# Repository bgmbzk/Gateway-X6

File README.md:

# Gateway-X6 — 6 Katmanlı STM32 Yüksek Hızlı Donanım Tasarımı

Gateway-X6; STM32 mikrokontrolcü mimarisi, harici SDRAM arayüzü ve endüstriyel haberleşme hatlarını bir araya getiren, sinyal bütünlüğü (Signal Integrity) ve güç dağıtımı (Power Distribution) önceliklendirilerek tasarlanmış 6 katmanlı (6-layer) bir PCB projesidir.

---

## 📸 Proje Görselleri

### 1. 3D Kart Görünümü

### 2. PCB Katman Çizimi ve Yönlendirme

### 3. Şematik Tasarım

---

## Proje Motivasyonu ve Öğrenim Hedefleri

Bu proje; hem profesyonel donanım tasarımı standartlarını pratiğe dökmek hem de karmaşık mimarilerle çalışırken karşılaşılan zorlukları bizzat tecrübe etmek amacıyla geliştirilmiştir:

- **STM32 Tasarım Standartları:** STM32 mikrokontrolcü ekosisteminin yüksek hızlı çevre birimleri, kristal osilatör hatları ve decoupling (dekaplaj) kondansatör yerleşim standartlarını derinlemesine uygulamak.
- **6 Katmanlı Yığın Yapısı (Stackup):** 2 veya 4 katmanlı yapıların ötesine geçerek, gürültü bağışıklığı ve kesintisiz referans düzlemleri (GND/PWR plane) sunan 6 katmanlı mimariyi deneyimlemek.
- **Sinyal ve Adres Hatlarında Karmaşıklık Yönetimi:** STM32 ile SDRAM arasındaki FMC (Flexible Memory Controller) arayüzünde yer alan onlarca yüksek hızlı veri, adres ve kontrol hattını (FMC_SDCKE, FMC_SDCLK vb.) çakışmasız, izole ve doğru pin eşlemeleriyle yönlendirmek; bu süreçteki etiketleme (net management) ve adresleme karmaşıklıklarını büyük bir sabır ve hassasiyetle çözmek.

---

## Katman Mimarisi (6-Layer Stackup)

Kartın sinyal bütünlüğünü korumak ve EMC/EMI performansını artırmak için aşağıdaki katman dizilimi uygulanmıştır:

1. **Top Layer (`F.Cu`):** Yüksek Hızlı Sinyaller ve Komponent Yerleşimi
2. **GND Plane (`GND`):** Üst Katman İçin Kesintisiz Toprak Referans Düzlemi
3. **Inner Signal (`SIG1`):** İç Sinyal Yönlendirme Katmanı
4. **GND2 Plane (`GND2`):** Güç Katmanı İçin İkincil Toprak Düzlemi
5. **Power Plane (`PWR`):** $+3.3\text{V}$ Besleme Düzlemi
6. **Bottom Layer (`B.Cu`):** Alt Sinyaller ve Kalın Güç Yolları ($+24\text{V}$, $+5\text{V}$)

---

## Güç Mimarisi ve Yönlendirme

- **$+24\text{V}$ Filtreli Endüstriyel Giriş:** Giriş gürültülerini bastıran filtreleme yapısı ve $1.0\text{ mm}$ kalınlığında yüksek akım hatları.
- **Kademeli Regülasyon:** $+24\text{V} \rightarrow +5\text{V}$ ve $+5\text{V} \rightarrow +3.3\text{V}$ ana hatlar üzerinden kararlı voltaj dağıtımı.
- **Hassas Sinyal İzolasyonu:** Hızlı saat hatları (FMC_SDCLK) ve kontrol hatları, hata ayıklama (SWCLK) ve güç hatlarından izole edilerek cross-talk (çapraz gürültü) engellenmiştir.

---

## Proje Dizin Yapısı

```text
Gateway-X6/
├── Hardware/               # KiCad şematik ve PCB çizim dosyaları (.kicad_sch, .kicad_pcb)
├── Production/             # Üretime hazır Gerber ve Drill ZIP dosyaları
├── Docs/                   # Şematik PDF çıktıları ve teknik dokümanlar
├── Images/                 # Proje görselleri (Gateway-X6.3d.png, Gateway-X6.pcb.png, Gateway-X6.kch.png)
├── .gitignore
└── README.md

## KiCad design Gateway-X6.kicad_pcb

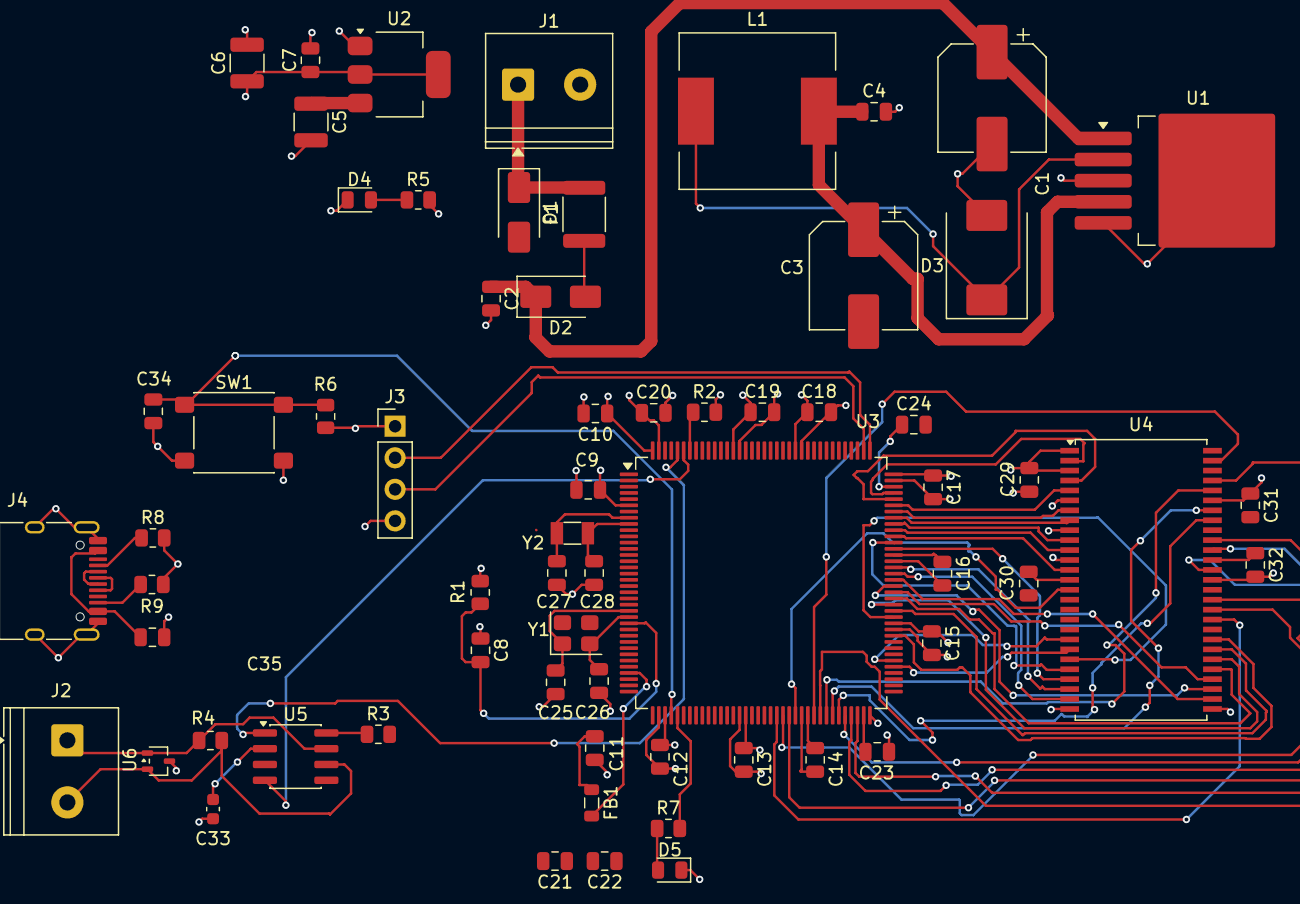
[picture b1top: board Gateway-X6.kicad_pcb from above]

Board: 6 copper layers, 65 parts (0 on the bottom side), 67 nets.

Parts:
C1: 100uF; CP_Elec_8x10.5
C2, C4, C7, C8, C9, C10, C11, C12, C13, C14, C15, C16, C17, C18, C19, C20, C22, C29, C30, C31, C32, C34, C35: 100nF; C_0805_2012Metric
C3: 220uF; CP_Elec_8x10.5
C5: 10uF; C_1210_3225Metric
C6: 220uF; C_1210_3225Metric
C21: 1uF; C_0805_2012Metric
C23, C24: 2.2uF; C_0805_2012Metric
C25, C26: 22pF; C_0805_2012Metric
C27, C28: 12pF; C_0805_2012Metric
C33: 100nF; C_0603_1608Metric
D1: D_TVS; D_SMA
D2: D_Schottky; D_SMA
D3: D_Schottky; D_SMC
D4, D5: LED; LED_0805_2012Metric
F1: Polyfuse; Fuse_1812_4532Metric
FB1: FerriteBead; L_0805_2012Metric
J1, J2: Screw_Terminal_01x02; TerminalBlock_Phoenix_PT-1,5-2-5.0-H_1x02_P5.00mm_Horizontal
J3: Conn_01x04_Pin; PinHeader_1x04_P2.54mm_Vertical
J4: USB_C_Receptacle_USB2.0_14P; USB_C_Receptacle_HRO_TYPE-C-31-M-12
L1: 33uF; L_12x12mm_H8mm
R1, R2: 10kΩ; R_0805_2012Metric
R3: 10k; R_0805_2012Metric
R4: 120; R_0805_2012Metric
R5, R7: 1k; R_0805_2012Metric
R6: 10 kΩ; R_0805_2012Metric
R8, R9: 5.1 kΩ; R_0805_2012Metric
SW1: SW_Push; SW_SPST_PTS645Sx43SMTR92
U1: LM2596S-5; TO-263-5_TabPin3
U2: AMS1117-3.3; SOT-223-3_TabPin2
U3: STM32F429ZITx; LQFP-144_20x20mm_P0.5mm
U4: IS42S16400J-xC; TSOP-II-54_22.2x10.16mm_P0.8mm
U5: SN65HVD230; SOIC-8_3.9x4.9mm_P1.27mm
U6: TPD2E2U06DCK; SOT-323_SC-70
Y1: 8 MHz; Crystal_SMD_3225-4Pin_3.2x2.5mm
Y2: 32.768 kHz; Crystal_SMD_3215-2Pin_3.2x1.5mm

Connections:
+3.3V: C6.1, C7.1, C9.1, C10.1, C11.1, C12.1, C13.1, C14.1, C15.1, C16.1, C17.1, C18.1, C19.1, C20.1, C29.1, C30.1, C31.1, C32.1, FB1.1, J3.1, R1.1, R5.2, R6.1, U2.2 (VO), U3.6 (VBAT), U3.17 (VDD), U3.30 (VDD), U3.39 (VDD), U3.52 (VDD), U3.62 (VDD), U3.72 (VDD), U3.84 (VDD), U3.95 (VDD), U3.108 (VDD), U3.121 (VDD), U3.131 (VDD), U3.143 (PDR_ON), U3.144 (VDD), U4.1 (VDD), U4.3 (VDDQ), U4.9 (VDDQ), U4.14 (VDD), U4.27 (VDD), U4.43 (VDDQ), U4.49 (VDDQ), U5.3 (VCC)
+5V: C3.1, C4.1, C5.1, L1.2, U1.4 (FB), U2.3 (VI)
+24V: D1.1 (A1), F1.2, J1.1
/+24V_FILT: C1.1, C2.1, D2.1 (K), U1.1 (VIN)
/CAN1_RX: U3.139 (PB8), U5.4 (R)
/CAN1_TX: U3.140 (PB9), U5.1 (D)
/FMC_A0: U3.97 (PC7), U4.23 (A0)
/FMC_A1: U3.96 (PC6), U4.24 (A1)
/FMC_A2: U3.93 (PG8), U4.25 (A2)
/FMC_A3: U3.92 (PG7), U4.26 (A3)
/FMC_A4: U3.91 (PG6), U4.29 (A4)
/FMC_A5: U3.90 (PG5), U4.30 (A5)
/FMC_A6: U3.89 (PG4), U4.31 (A6)
/FMC_A7: U3.88 (PG3), U4.32 (A7)
/FMC_A8: U3.87 (PG2), U4.33 (A8)
/FMC_A9: U3.86 (PD15), U4.34 (A9)
/FMC_A10: U3.85 (PD14), U4.22 (A10)
/FMC_A11: U3.82 (PD13), U4.35 (A11)
/FMC_BA0: U3.78 (PD9), U4.20 (BA0)
/FMC_BA1: U3.77 (PD8), U4.21 (BA1)
/FMC_D0: U3.105 (PA13), U4.2 (DQ0)
/FMC_D1: U3.104 (PA12), U4.4 (DQ1)
/FMC_D2: U3.103 (PA11), U4.5 (DQ2)
/FMC_D3: U3.102 (PA10), U4.7 (DQ3)
/FMC_D4: U3.101 (PA9), U4.8 (DQ4)
/FMC_D5: U3.100 (PA8), U4.10 (DQ5)
/FMC_D6: U3.99 (PC9), U4.11 (DQ6)
/FMC_D7: U3.98 (PC8), U4.13 (DQ7)
/FMC_D8: U3.70 (PB11), U4.42 (DQ8)
/FMC_D9: U3.69 (PB10), U4.44 (DQ9)
/FMC_D10: U3.68 (PE15), U4.45 (DQ10)
/FMC_D11: U3.67 (PE14), U4.47 (DQ11)
/FMC_D12: U3.66 (PE13), U4.48 (DQ12)
/FMC_D13: U3.65 (PE12), U4.50 (DQ13)
/FMC_D14: U3.64 (PE11), U4.51 (DQ14)
/FMC_D15: U3.63 (PE10), U4.53 (DQ15)
/FMC_NBL0: U3.60 (PE9), U4.15 (LDQM)
/FMC_NBL1: U3.59 (PE8), U4.39 (UDQM)
/FMC_SDCKE: U3.57 (PG1), U4.37 (CKE)
/FMC_SDCLK: U3.58 (PE7), U4.38 (CLK)
/MCU_LED: R7.2, U3.41 (PA5)
/SWCLK: J3.3, U3.110 (PA15)
/SWDIO: J3.2, U3.109 (PA14)
/USB_DM: J4.A7 (D-), J4.B7 (D-)
/USB_DP: J4.A6 (D+), J4.B6 (D+)
/USB_VBUS: C35.1, J4.A4 (VBUS), J4.A9 (VBUS), J4.B4 (VBUS), J4.B9 (VBUS)
/USER_BTN: C34.1, R6.2, SW1.1, U3.40 (PA4)
GND: C1.2, C2.2, C3.2, C4.2, C5.2, C6.2, C7.2, C8.1, C9.2, C10.2, C11.2, C12.2, C13.2, C14.2, C15.2, C16.2, C17.2, C18.2, C19.2, C20.2, C21.1, C22.1, C23.2, C24.2, C25.2, C26.2, C27.2, C28.2, C29.2, C30.2, C31.2, C32.2, C33.2, C34.2, C35.2, D1.2 (A2), D3.2 (A), D4.1 (K), D5.1 (K), J1.2, J3.4, J4.A1 (GND), J4.A12 (GND), J4.B1 (GND), J4.B12 (GND), J4.SH (SHIELD), R2.2, R3.2, R8.2, R9.2, SW1.2, U1.3 (GND), U1.5 (~ON/OFF), U2.1 (GND), U3.16 (VSS), U3.31 (VSSA), U3.32 (VREF+), U3.38 (VSS), U3.51 (VSS), U3.61 (VSS), U3.83 (VSS), U3.94 (VSS), U3.107 (VSS), U3.120 (VSS), U3.130 (VSS), U4.6 (GNDQ), U4.12 (GNDQ), U4.28 (GND), U4.41 (GND), U4.46 (GNDQ), U4.52 (GNDQ), U4.54 (GND), U6.3
unnamed: D2.2 (A), F1.1
unnamed: D3.1 (K), L1.1, U1.2 (OUT)
unnamed: D4.2 (A), R5.1
unnamed: D5.2 (A), R7.1
unnamed: J2.1, R4.1, U5.7 (CANH), U6.1
unnamed: J2.2, R4.2, U5.6 (CANL), U6.2
unnamed: J4.A5 (CC1), R8.1
unnamed: J4.B5 (CC2), R9.1
unnamed: R2.1, U3.138 (BOOT0)
unnamed: C8.2, R1.2, U3.25 (NRST)
unnamed: C27.1, U3.8 (PC14), Y2.1
unnamed: C28.1, U3.9 (PC15), Y2.2
unnamed: C25.1, U3.23 (PH0), Y1.1
unnamed: C26.1, U3.24 (PH1), Y1.2
unnamed: C23.1, U3.71 (VCAP_1)
unnamed: C24.1, U3.106 (VCAP_2)
unnamed: C21.2, C22.2, FB1.2, U3.33 (VDDA)
unnamed: C33.1, U5.2 (GND)
unnamed: R3.1, U5.8 (Rs)
